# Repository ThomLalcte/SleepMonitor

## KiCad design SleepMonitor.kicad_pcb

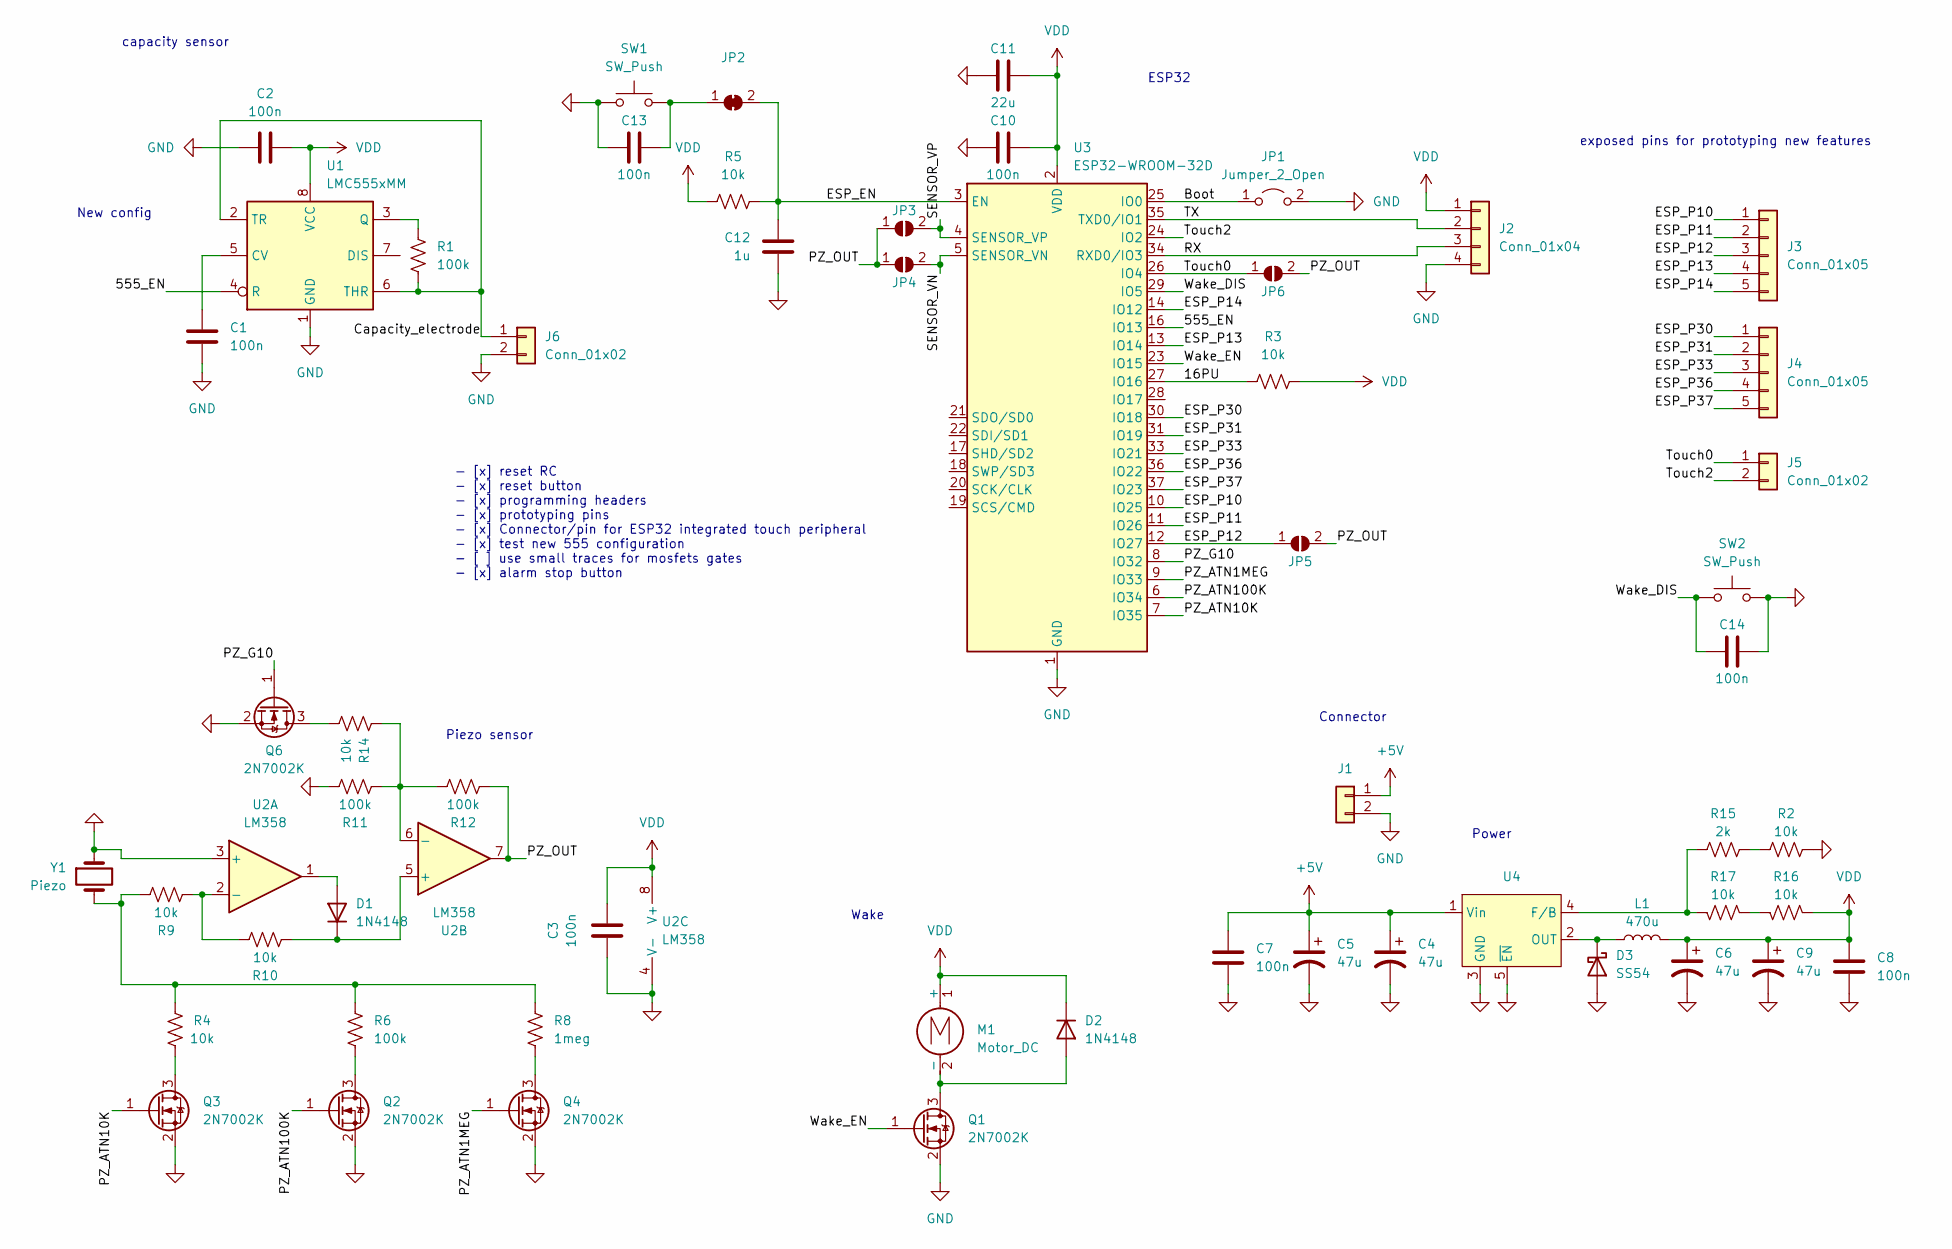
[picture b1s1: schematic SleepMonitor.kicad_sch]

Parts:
C1, C2, C3, C7, C8, C10, C13, C14: 100n; C_0805_2012Metric_Pad1.18x1.45mm_HandSolder
C4, C5, C6, C9: 47u; CP_Elec_6.3x5.7
C11: 22u; C_1812_4532Metric_Pad1.57x3.40mm_HandSolder
C12: 1u; C_0805_2012Metric_Pad1.18x1.45mm_HandSolder
D1, D2: 1N4148; D_DO-35_SOD27_P7.62mm_Horizontal
D3: SS54; D_SMA_Handsoldering
J1, J5, J6: Conn_01x02; PinHeader_1x02_P2.54mm_Vertical
J2: Conn_01x04; PinHeader_1x04_P2.54mm_Vertical
J3, J4: Conn_01x05; PinHeader_1x05_P2.54mm_Vertical
JP1: Jumper_2_Open; TestPoint_2Pads_Pitch2.54mm_Drill0.8mm
JP2: SolderJumper_2_Bridged; SolderJumper-2_P1.3mm_Open_TrianglePad1.0x1.5mm
JP3, JP4, JP5, JP6: SolderJumper_2_Open; SolderJumper-2_P1.3mm_Open_TrianglePad1.0x1.5mm
L1: 470u; L_12x12mm_H8mm
M1: Motor_DC; PinHeader_1x02_P2.54mm_Vertical
Q1, Q2, Q3, Q4, Q6: 2N7002K; SOT-23-3
R1, R6, R11, R12: 100k; R_0805_2012Metric_Pad1.20x1.40mm_HandSolder
R2, R3, R4, R5, R9, R10, R14, R16, R17: 10k; R_0805_2012Metric_Pad1.20x1.40mm_HandSolder
R8: 1meg; R_0805_2012Metric_Pad1.20x1.40mm_HandSolder
R15: 2k; R_0805_2012Metric_Pad1.20x1.40mm_HandSolder
SW1, SW2: SW_Push; SW_Push_1P1T_NO_Vertical_Wuerth_434133025816
U1: LMC555xMM; VSSOP-8_3.0x3.0mm_P0.65mm
U2: LM358; SOIC-8_3.9x4.9mm_P1.27mm
U3: ESP32-WROOM-32D
U4: TO-263-5_TabPin3
Y1: Piezo; PinHeader_1x02_P2.54mm_Vertical

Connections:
+5V: C4.1, C5.1, C7.1, J1.1, U4.1 (Vin)
/16PU: R3.1, U3.27 (IO16)
/555_EN: U1.4 (R), U3.16 (IO13)
/Boot: JP1.1 (A), U3.25 (IO0)
/Capacity_electrode: J6.1, R1.2, U1.2 (TR), U1.6 (THR)
/ESP_EN: C12.1, JP2.2 (B), R5.2, U3.3 (EN)
/ESP_P10: J3.1, U3.10 (IO25)
/ESP_P11: J3.2, U3.11 (IO26)
/ESP_P12: J3.3, JP5.1 (A), U3.12 (IO27)
/ESP_P13: J3.4, U3.13 (IO14)
/ESP_P14: J3.5, U3.14 (IO12)
/ESP_P30: J4.1, U3.30 (IO18)
/ESP_P31: J4.2, U3.31 (IO19)
/ESP_P33: J4.3, U3.33 (IO21)
/ESP_P36: J4.4, U3.36 (IO22)
/ESP_P37: J4.5, U3.37 (IO23)
/PZ_ATN1MEG: Q4.1 (G), U3.9 (IO33)
/PZ_ATN10K: Q3.1 (G), U3.7 (IO35)
/PZ_ATN100K: Q2.1 (G), U3.6 (IO34)
/PZ_G10: Q6.1 (G), U3.8 (IO32)
/PZ_OUT: JP3.1 (A), JP4.1 (A), JP5.2 (B), JP6.2 (B), R12.1, U2.7
/RX: J2.3, U3.34 (RXD0/IO3)
/SENSOR_VN: JP4.2 (B), U3.5 (SENSOR_VN)
/SENSOR_VP: JP3.2 (B), U3.4 (SENSOR_VP)
/TX: J2.2, U3.35 (TXD0/IO1)
/Touch0: J5.1, JP6.1 (A), U3.26 (IO4)
/Touch2: J5.2, U3.24 (IO2)
/Wake_DIS: C14.1, SW2.1, U3.29 (IO5)
/Wake_EN: Q1.1 (G), U3.23 (IO15)
GND: C1.2, C2.1, C3.1, C4.2, C5.2, C6.2, C7.2, C8.2, C9.2, C10.1, C11.1, C12.2, C13.1, C14.2, D3.2 (A), J1.2, J2.4, J6.2, JP1.2 (B), Q1.2 (S), Q2.2 (S), Q3.2 (S), Q4.2 (S), Q6.2 (S), R2.2, R11.2, SW1.1, SW2.2, U1.1 (GND), U2.3 (+), U2.4 (V-), U3.1 (GND), U3.15 (GND), U3.38 (GND), U3.39 (GND), U4.3 (GND), U4.5 (~EN), Y1.1
unnamed: D1.2 (A), U2.1
unnamed: D1.1 (K), R10.1, U2.5 (+)
unnamed: D2.2 (A), M1.2 (-), Q1.3 (D)
unnamed: D3.1 (K), L1.1, U4.2 (OUT)
unnamed: C13.2, JP2.1 (A), SW1.2
unnamed: Q2.3 (D), R6.1
unnamed: Q3.3 (D), R4.1
unnamed: Q4.3 (D), R8.1
unnamed: Q6.3 (D), R14.1
unnamed: R4.2, R6.2, R8.2, R9.2, Y1.2
unnamed: R2.1, R15.2
unnamed: R16.2, R17.1
unnamed: C1.1, U1.5 (CV)
unnamed: R1.1, U1.3 (Q)
unnamed: R9.1, R10.2, U2.2 (-)
unnamed: R11.1, R12.2, R14.2, U2.6 (-)
unnamed: R15.1, R17.2, U4.4 (F/B)
VDD: C2.2, C3.2, C6.1, C8.1, C9.1, C10.2, C11.2, D2.1 (K), J2.1, L1.2, M1.1 (+), R3.2, R5.1, R16.1, U1.8 (VCC), U2.8 (V+), U3.2 (VDD)

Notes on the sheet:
Power
New config
capacity sensor
Piezo sensor
ESP32
Wake
exposed pins for prototyping new features
- [x] reset RC - [x] reset button - [x] programming headers - [x] prototyping pins - [x] Connector/pin for ESP32 integrated touch peripheral - [x] test new 555 configuration - [ ] use small traces for mosfets gates - [x] alarm stop button
Connector

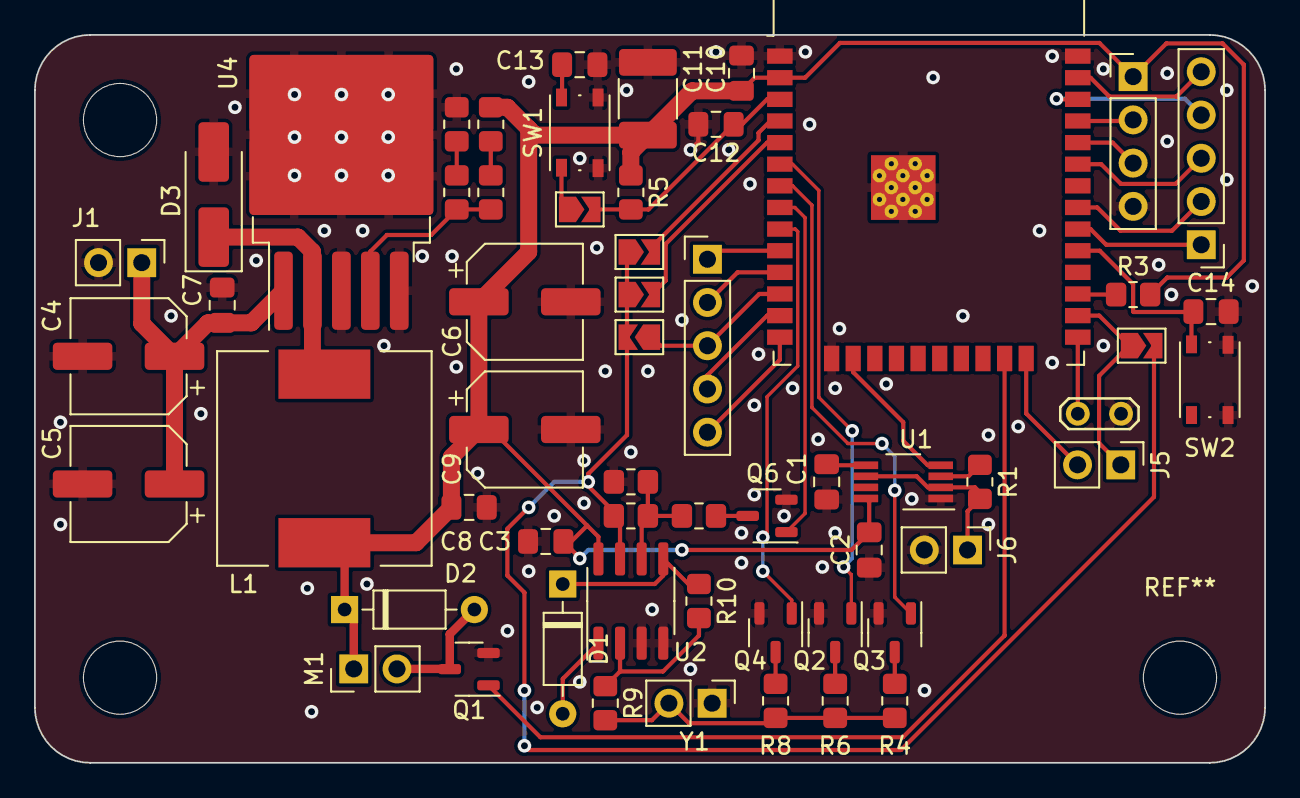
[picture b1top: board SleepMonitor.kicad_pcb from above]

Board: 2 copper layers, 72.2 x 42.8 mm, 58 parts (0 on the bottom side), 48 nets.

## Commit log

2024-01-16 init
